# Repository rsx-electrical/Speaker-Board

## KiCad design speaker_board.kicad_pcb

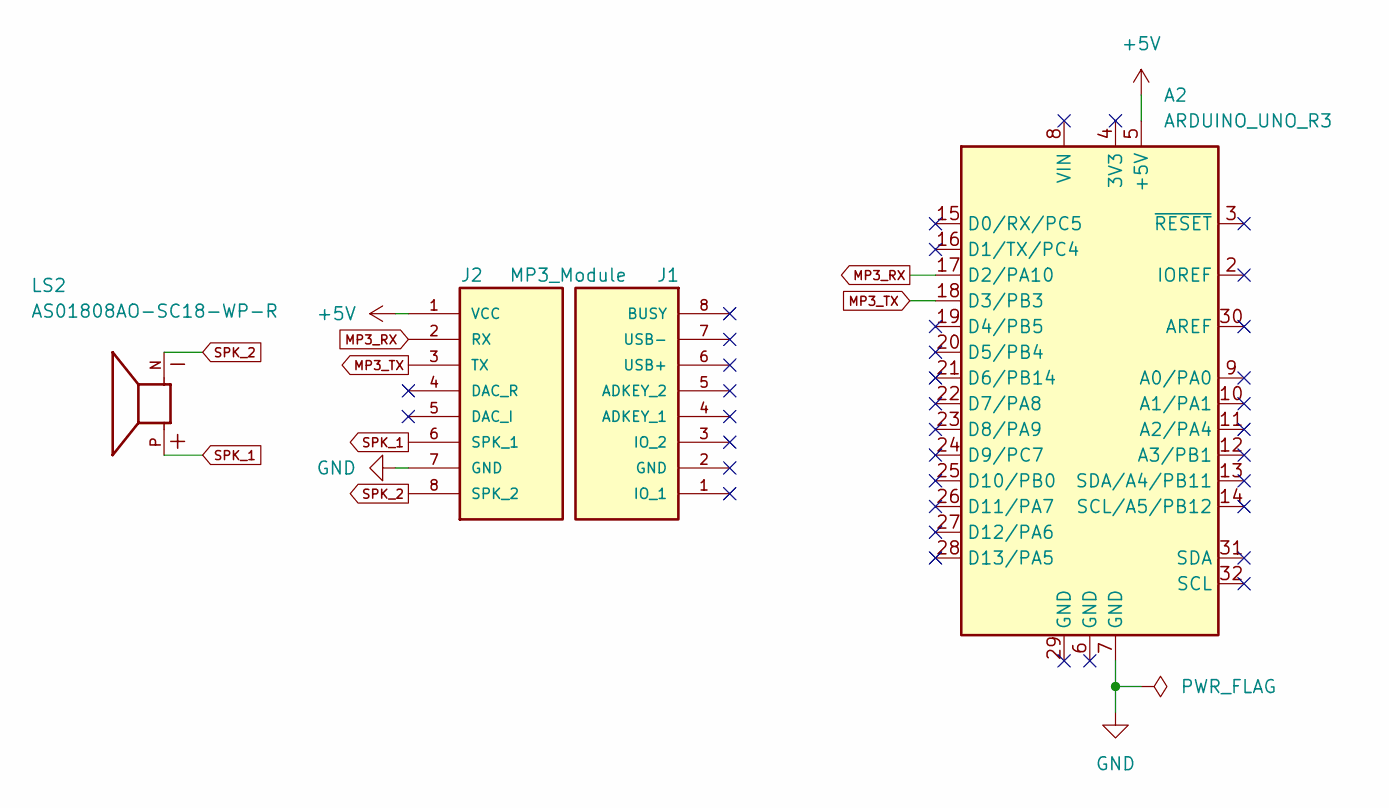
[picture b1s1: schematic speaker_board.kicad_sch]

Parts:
A2: ARDUINO_UNO_R3; STM32_NUCLEO64_ArduinoUno; MPN PRT-11417
J1: SSK02-FPH-254-A8; SAMESKY_SSK02-FPH-254-A8; MPN SSK02-FPH-254-A8
J2: MP3_Module; SAMESKY_SSK02-FPH-254-A8; MPN SSK02-FPH-254-A8
LS2: AS01808AO-SC18-WP-R; SPKR_AS01808AO-SC18-WP-R; PARTREV B

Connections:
+5V: A2.5 (+5V), J2.1 (VCC)
GND: A2.7 (GND), J2.7 (GND)
MP3_RX: A2.17 (D2/PA10), J2.2 (RX)
MP3_TX: A2.18 (D3/PB3), J2.3 (TX)
SPK_1: J2.6 (SPK_1), LS2.P
SPK_2: J2.8 (SPK_2), LS2.N

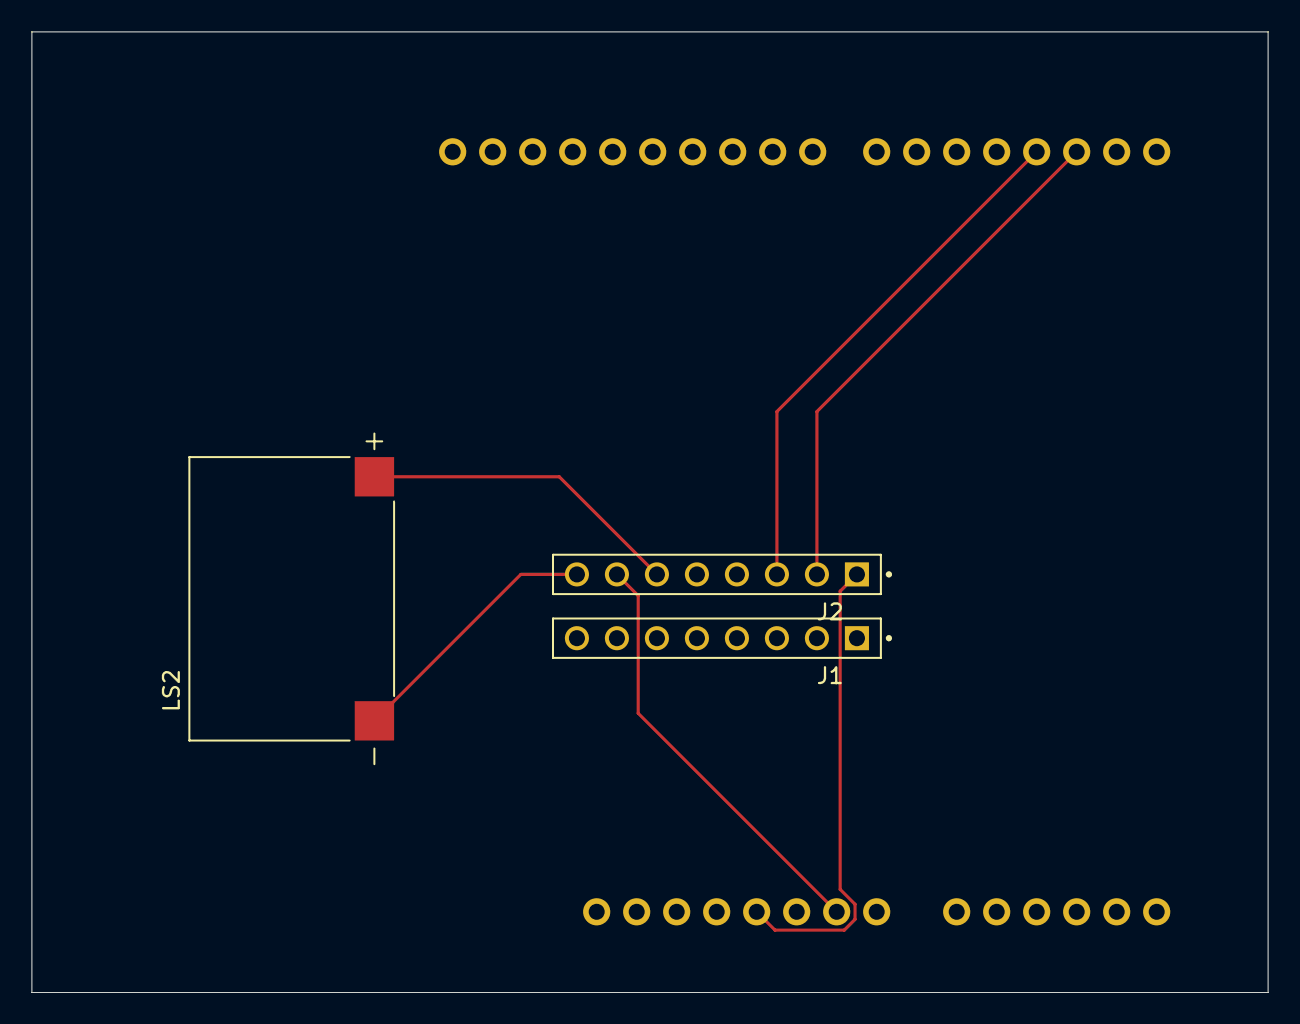
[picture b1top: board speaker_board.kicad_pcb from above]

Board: 2 copper layers, 78.5 x 61.0 mm, 5 parts (0 on the bottom side), 6 nets.

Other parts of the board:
A1: ARDUINO_UNO_R3; Arduino_UNO_R3_WithMountingHoles
